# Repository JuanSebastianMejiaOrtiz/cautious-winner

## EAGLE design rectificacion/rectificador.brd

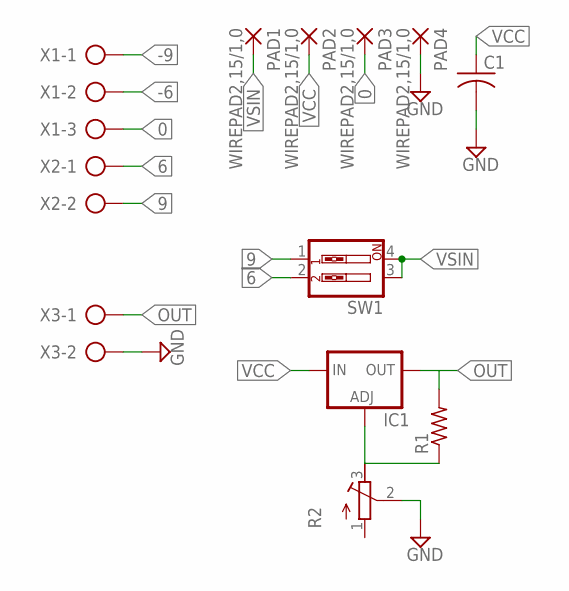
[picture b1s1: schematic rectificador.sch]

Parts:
C1: C-US050-024X044; C050-024X044
IC1: LM317TS; 317TS
PAD1, PAD2, PAD3, PAD4: WIREPAD2,15/1,0; 2,15/1,0
R1: R-US_0204/7; 0204/7
R2: R-TRIMM64W; RTRIM64W
SW1: SW_DIP-2; EDG-02
X1: AK300/3
X2, X3: AK300/2

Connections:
0: PAD3.1, X1.3
6: SW1.2, X2.1
9: SW1.1, X2.2
-6: X1.2
-9: X1.1
GND: C1.2, PAD4.1, R2.2 (S), X3.2
unnamed: IC1.1 (ADJ), R1.1, R2.3 (E)
OUT: IC1.2 (OUT), R1.2, X3.1
VCC: C1.1, IC1.3 (IN), PAD2.1
VSIN: PAD1.1, SW1.3, SW1.4

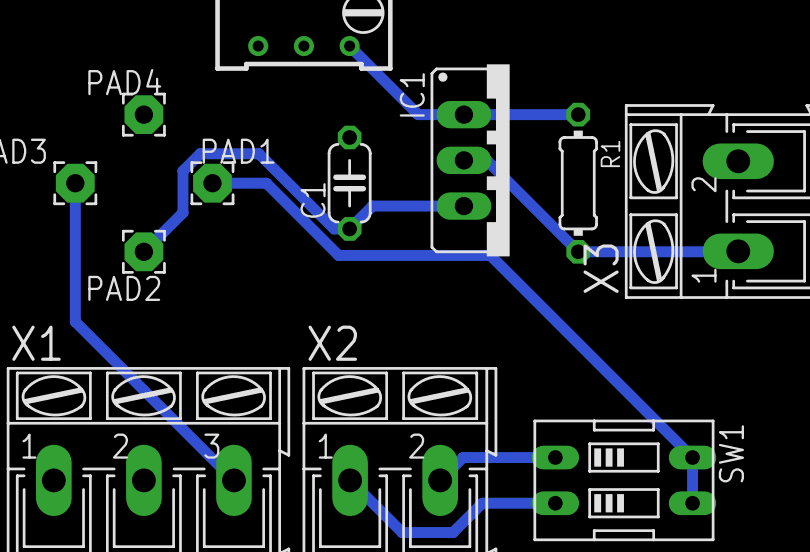
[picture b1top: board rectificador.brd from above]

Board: 2 copper layers, 12 parts (0 on the bottom side), 8 nets.

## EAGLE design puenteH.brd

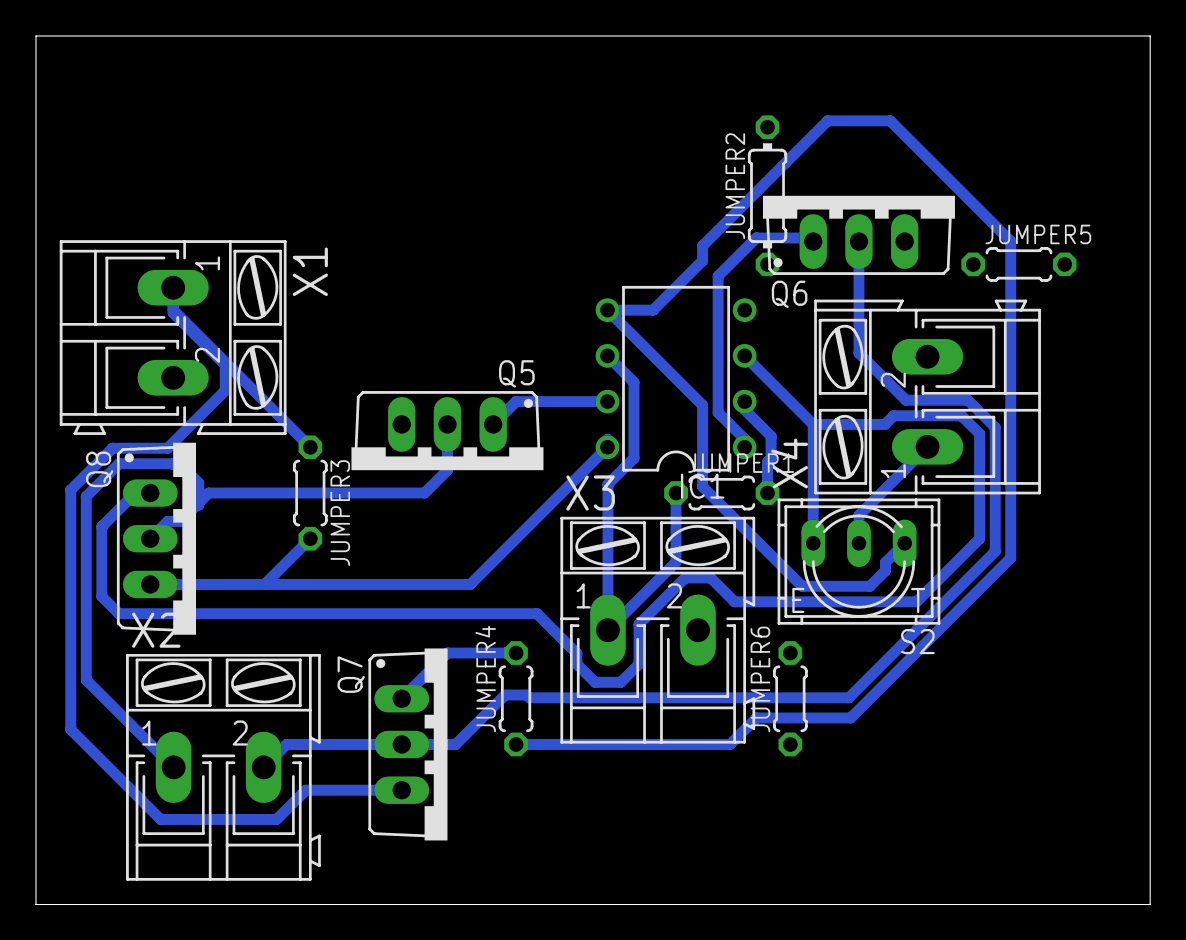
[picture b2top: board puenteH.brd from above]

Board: 2 copper layers, 61.9 x 48.2 mm, 16 parts (0 on the bottom side), 10 nets.

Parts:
IC1: LM393N; DIL08
JUMPER1, JUMPER3, JUMPER4, JUMPER5, JUMPER6: 0204/5
JUMPER2: 0204/7
Q5, Q6: IRF540; TO220BV
Q7, Q8: IRF9530; TO220BV
S2: 9077-1
X1, X2, X3, X4: AK300/2

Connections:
0: IC1.4, JUMPER2.1, JUMPER2.2, JUMPER5.1, JUMPER5.2, JUMPER6.1, JUMPER6.2, Q5.S, Q6.S, X1.2, X3.2, X4.2
CONTROL: S2.2, X4.1
DER: IC1.3, Q8.G, S2.3
IZQ: IC1.5, JUMPER4.1, JUMPER4.2, Q7.G, S2.1
MOTOR_DER: Q6.D, Q7.D, X2.2
MOTOR_IZQ: Q5.D, Q8.D, X2.1
PWM: IC1.2, IC1.6, JUMPER1.1, JUMPER1.2, X3.1
VCC: IC1.8, JUMPER3.1, JUMPER3.2, Q7.S, Q8.S, X1.1
VDER: IC1.1, Q6.G
VIZQ: IC1.7, Q5.G

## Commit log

2025-11-30 Using the components that in reality are going to be added, not finished
2025-11-30 Ready to get gerbers, a little optimized, not using 'compontents that are really going to be used' but it is good enough
2025-11-30 Board using real components ready, just need to verify that they in fact exist (or that it is possible to find them at the store)
2025-11-30 Board compacted a little more. Also added .gitignore
2025-11-30 Adding .gitignore
2025-12-01 Added Pseudo-constant voltage source
2025-12-01 Added Pseudo-constant voltage source design, still needs the regulator (INCOMPLETE)
2025-12-01 Output folder ignored
2025-12-01 Regulator ready to get gerbers
